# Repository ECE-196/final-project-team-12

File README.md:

We developed a device to assist drivers with parking, specifically in compact spots. This will be done with a LiDAR sensor that will map a 2D birds eye view of obstacles in front and to the side of the car. This map will then be displayed on a screen for the driver to see and make judgements accordingly while parking. The device will assist the driver to measure the dimensions of a parking spot and help judge whether or not it is too compact to park in. 

This repository contains all the files and progression pictures/videos used to develop this product.

See our [Website](https://sites.google.com/ucsd.edu/team-12?usp=sharing) for more information

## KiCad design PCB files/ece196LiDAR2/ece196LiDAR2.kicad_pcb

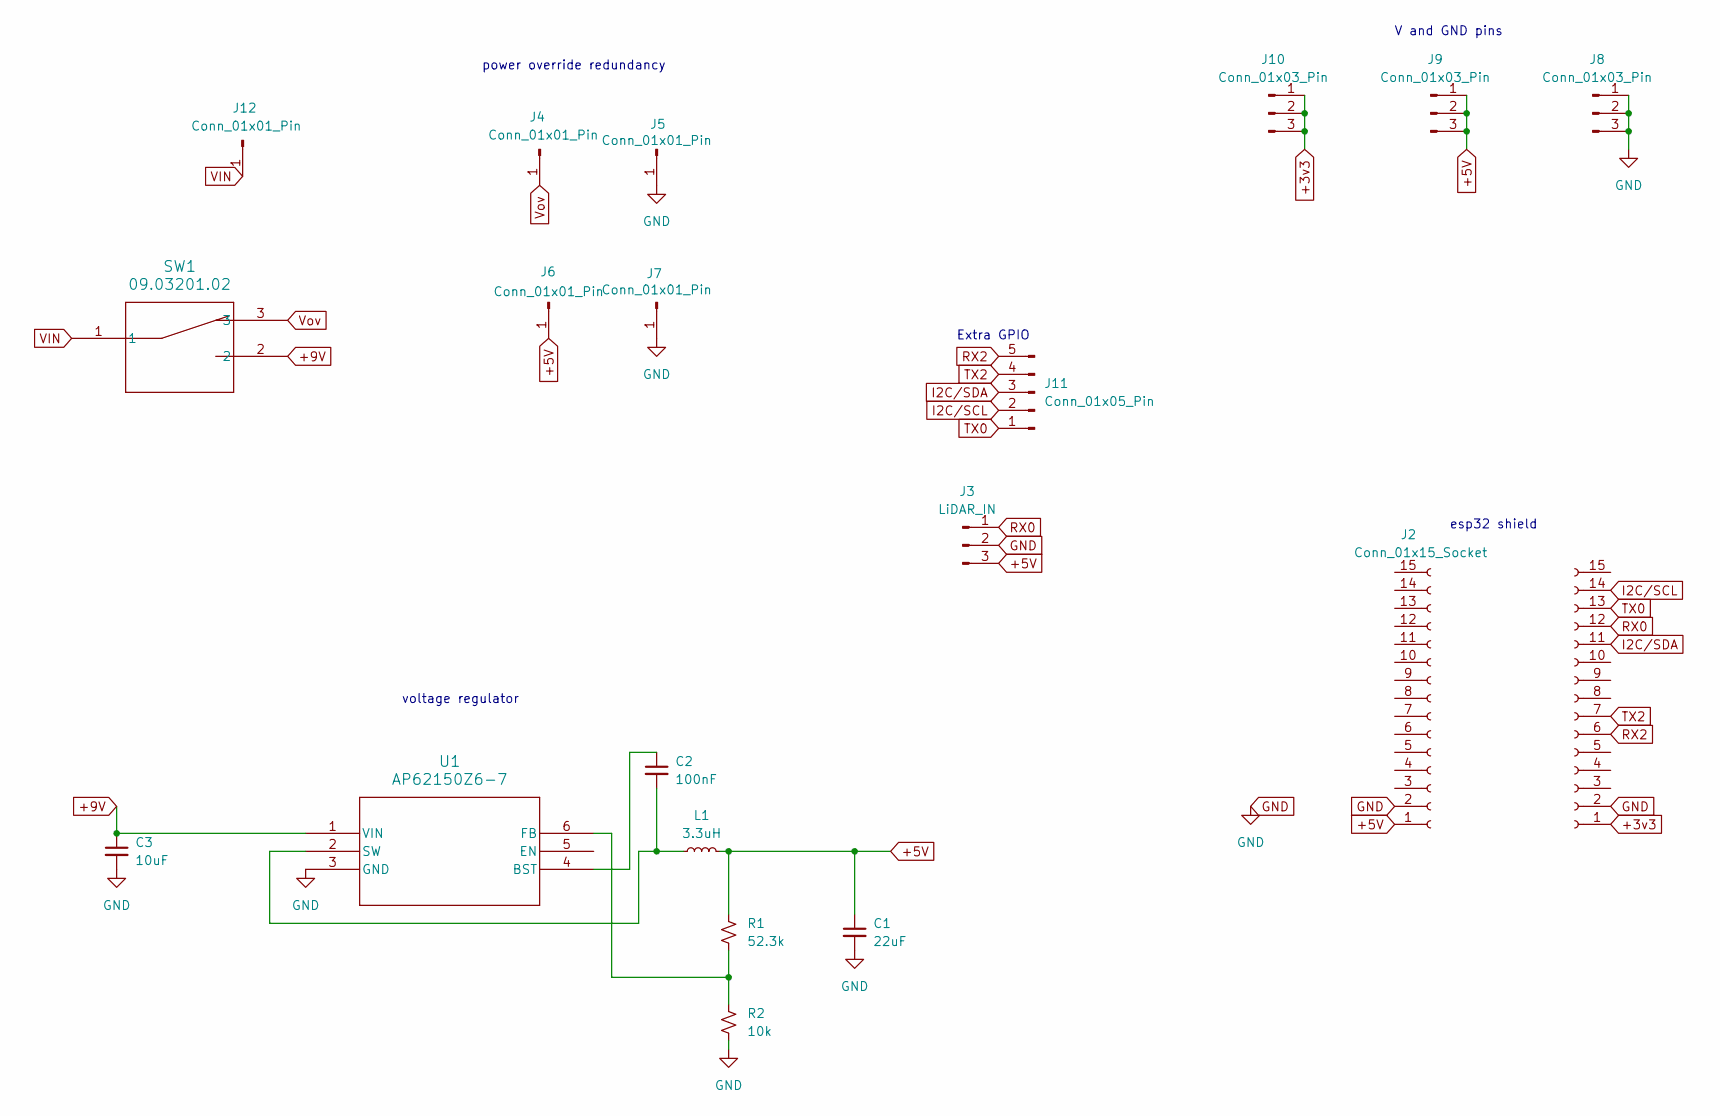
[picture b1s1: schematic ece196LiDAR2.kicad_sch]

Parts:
C1: 22uF; C_0805_2012Metric
C2: 100nF; C_0805_2012Metric
C3: 10uF; C_0805_2012Metric
J1, J2: Conn_01x15_Socket; PinHeader_1x15_P2.54mm_Vertical
J3: LiDAR_IN; PinHeader_1x03_P2.54mm_Vertical
J4, J5, J6, J7, J12: Conn_01x01_Pin; PinHeader_1x01_P2.54mm_Vertical
J8, J9, J10: Conn_01x03_Pin; PinHeader_1x03_P2.54mm_Vertical
J11: Conn_01x05_Pin; PinHeader_1x05_P2.54mm_Vertical
L1: 3.3uH; L_0805_2012Metric
R1: 52.3k; R_0805_2012Metric
R2: 10k; R_0805_2012Metric
SW1: 09.03201.02; 09.03201_EAO
U1: AP62150Z6-7; SOT563_DIO

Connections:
+3v3: J1.1, J10.1, J10.2, J10.3
+5V: C1.1, J2.1, J3.3, J6.1, J9.1, J9.2, J9.3, L1.2, R1.1
+9V: C3.1, SW1.2, U1.1 (VIN)
GND: C1.2, C3.2, J1.2, J2.2, J3.2, J5.1, J7.1, J8.1, J8.2, J8.3, R2.2, U1.3 (GND)
I2C/SCL: J1.14, J11.2
I2C/SDA: J1.11, J11.3
unnamed: C2.1, U1.4 (BST)
unnamed: R1.2, R2.1, U1.6 (FB)
unnamed: C2.2, L1.1, U1.2 (SW)
RX0: J1.12, J3.1
RX2: J1.6, J11.5
TX0: J1.13, J11.1
TX2: J1.7, J11.4
VIN: J12.1, SW1.1
Vov: J4.1, SW1.3

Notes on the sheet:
voltage regulator
Extra GPIO
V and GND pins
esp32 shield
power override redundancy

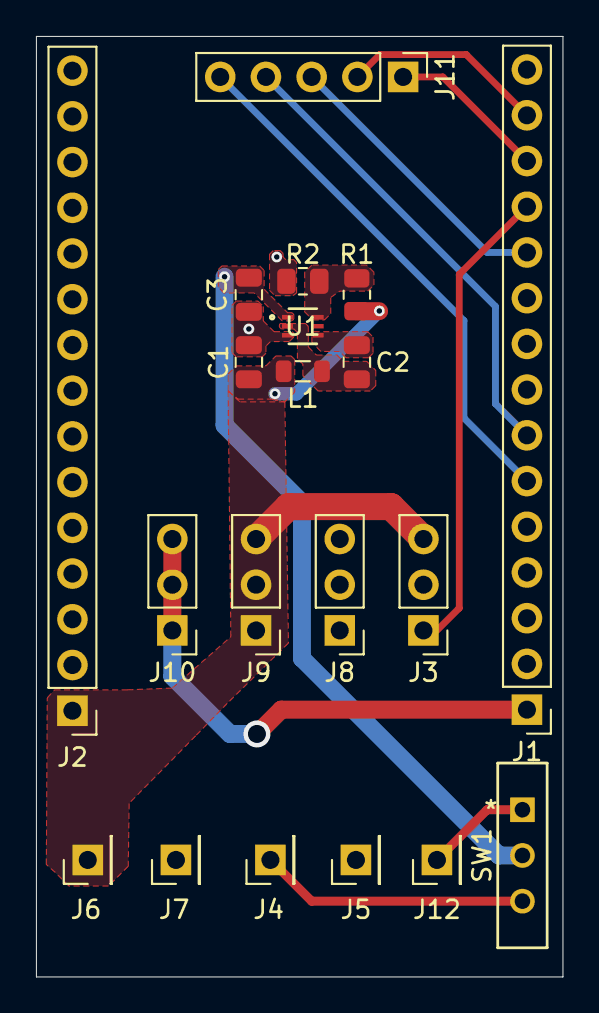
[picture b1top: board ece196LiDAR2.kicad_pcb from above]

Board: 2 copper layers, 29.2 x 52.2 mm, 20 parts (0 on the bottom side), 15 nets.

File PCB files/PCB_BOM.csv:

Reference,Value,Datasheet,Footprint,Qty,DNP,Digikey part #
C1,22uF,~,Capacitor_SMD:C_0805_2012Metric,1,,1276-2909-1-ND 
C2,100nF,~,Capacitor_SMD:C_0805_2012Metric,1,,1276-1782-1-ND 
C3,10uF,~,Capacitor_SMD:C_0805_2012Metric,1,,1276-1096-1-ND 
"J1,J2",Conn_01x15_Socket,~,Connector_PinHeader_2.54mm:PinHeader_1x15_P2.54mm_Vertical,2,,S7013-ND
J3,LiDAR_IN,~,Connector_PinHeader_2.54mm:PinHeader_1x03_P2.54mm_Vertical,1,,S7001-ND
"J4,J5,J6,J7,J12",Conn_01x01_Pin,~,Connector_PinHeader_2.54mm:PinHeader_1x01_P2.54mm_Vertical,5,,A26540-ND
"J8,J9,J10",Conn_01x03_Pin,~,Connector_PinHeader_2.54mm:PinHeader_1x03_P2.54mm_Vertical,3,,732-5316-ND
J11,Conn_01x05_Pin,~,Connector_PinHeader_2.54mm:PinHeader_1x05_P2.54mm_Vertical,1,,732-5318-ND
L1,3.3uH,~,Inductor_SMD:L_0805_2012Metric,1,,2035-1251-1-ND
R1,52.3k,~,Resistor_SMD:R_0805_2012Metric,1,,541-52.3KCCT-ND
R2,10k,~,Resistor_SMD:R_0805_2012Metric,1,,RR12P10.0KDCT-ND
SW1,sw1,,09.03201.02,1,,1948-1086-ND
U1,AP62150Z6-7,AP62150Z6-7,KiCADv6:SOT563_DIO,1,,31-AP62150Z6-7CT-ND

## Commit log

2024-10-28 Submitting PCB schematic + weekend progress
2024-10-30 PCB submission
2024-10-31 Updated PCB
2024-10-31 updated PCB again
2024-10-31 connected 5v trace
2024-11-27 changed anme
2024-12-02 my contributions
2024-12-02 my contribution
2024-12-03 demo videos
    First videos of the lidar working
2024-12-03 final code backups
2024-12-03 Create Scrips.docx
    Scripts that I as a screenwriter made for our video
2024-12-03 Updated directory
2024-12-04 My contribution
    I contributed most part of the poster design.
2024-12-07 (one of the) final updates
2024-12-07 reformatting
2024-12-07 uploading pictures and videos
2024-12-09 organizing repo
    hopefully the real last push I make
